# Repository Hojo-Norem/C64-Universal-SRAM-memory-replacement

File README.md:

# C64-Universal-SRAM-memory-replacement
Replace that old unreliable DRAM in your C64 with SRAM!

Inspired by penfold42 on the Lemon64 forum.

Bonus for shortboard users!
---------------------------------------
Testing so far has shown that this mod eliminates the VSP bug!

The main goal of this little experiment is to see if the SRAM has any immunity to the VIC-II VSP bug that plagues many shortboard C64s and some longboard C64s.

This board has been designed to fit under the character generator ROM on either the long or short motherboards.  It will also work in the KERNAL and BASIC sockets on the long board.

Basic construction
-------------------------

64KB, 128KB and 256KB SRAMs in a "SOP32L" or similar package,  are compatible as long as they conform to the standard pinout.  64KB SRAMS can be harvested (carefully) from SNES Stuntrace FX and DooM carts.  128KB SRAMS are still relatively easy to come by new (as of 2016).  Use those, cause destroying working carts for parts is a crime...  Okay, it /should/ be. 

C1 and C2 are basic power bypass caps.  I just used some spare 100nf parts I had lying around.

The small IC just above the caps is a single inverter gate.  There are differing part numbers among the various manufactures, but what you are looking for is a inverter in a SOT23-5 package designed for 5V operation.  It would probably help to get the TTL compatible version.  The part number printed (74HCT1G04) is a guide only.

Header Wiring
--------------------
Pins 1,3,4 & 5 connect the the motherboard's DRAM address lines MA4, MA5, MA6 & MA7.  For the 4146s used on most longboards, these are pins 9,10,11 & 13.  For the 41464 used on the shortboards and later longboards, use pins 7,8,10 & 14.  Do not cross check these with the datasheets as Commodore did not.  Following the datasheet (for the 41464 at least) will result in screen corruption and a lower bytes free reported on bootup.  These can be connected in any order, Commodore didn't care and so doesn't the memory!

Pin 2 is connected to the DRAM R/W line, which is pin 3 and 4 for the 4146 and 41464 respectively.

Pin 6 is connected to the DRAM CAS line.  Pin 15 for the 4146 and pin 16 for the 41464.

Finally, pin 7 is connected to the DRAM RAS line.  Pin 4 for the 4146 and pin 5 for the 41464.

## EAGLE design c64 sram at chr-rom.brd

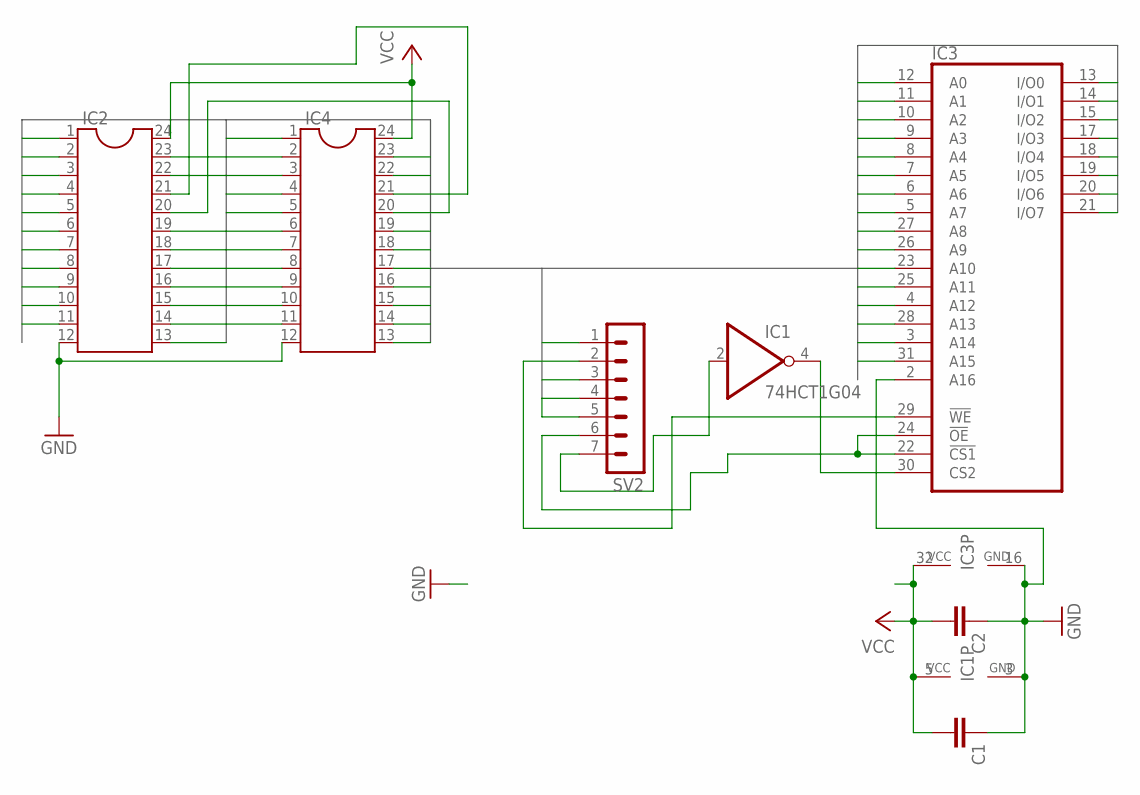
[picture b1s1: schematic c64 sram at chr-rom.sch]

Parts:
C1, C2: C-EUC0805; C0805
IC1: 74HCT1G04; SOT23-5
IC2, IC4: DIL24-6
IC3: LP621024CM; SOP32L
SV2: MA07-1

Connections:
A0: IC2.8, IC3.12 (A0), IC4.8
A1: IC2.7, IC3.11 (A1), IC4.7
A2: IC2.6, IC3.10 (A2), IC4.6
A3: IC2.5, IC3.9 (A3), IC4.5
A4: IC2.4, IC3.8 (A4), IC4.4
A5: IC2.3, IC3.7 (A5), IC4.3
A6: IC2.2, IC3.6 (A6), IC4.2
A7: IC2.1, IC3.5 (A7), IC4.1
A8: IC2.23, IC3.27 (A8), IC4.23
A9: IC2.22, IC3.26 (A9), IC4.22
A10: IC2.19, IC3.23 (A10), IC4.19
A11: IC2.18, IC3.25 (A11), IC4.18
A12: IC3.4 (A12), SV2.5
A13: IC3.28 (A13), SV2.3
A14: IC3.3 (A14), SV2.4
A15: IC3.31 (A15), SV2.1
D0: IC2.9, IC3.13 (I/O0), IC4.9
D1: IC2.10, IC3.14 (I/O1), IC4.10
D2: IC2.11, IC3.15 (I/O2), IC4.11
D3: IC2.13, IC3.21 (I/O7), IC4.13
D4: IC2.14, IC3.20 (I/O6), IC4.14
D5: IC2.15, IC3.19 (I/O5), IC4.15
D6: IC2.16, IC3.18 (I/O4), IC4.16
D7: IC2.17, IC3.17 (I/O3), IC4.17
GND: C1.1, C2.1, IC1.3 (GND), IC2.12, IC3.2 (A16), IC3.16 (GND), IC4.12
unnamed: IC2.21, IC4.21
unnamed: IC1.4 (O), IC3.30 (CS2)
unnamed: IC2.20, IC4.20
unnamed: IC1.2 (I), SV2.7
unnamed: IC3.22 (!CS1), IC3.24 (!OE), SV2.6
R/_W: IC3.29 (!WE), SV2.2
VCC: C1.2, C2.2, IC1.5 (VCC), IC2.24, IC3.32 (VCC), IC4.24

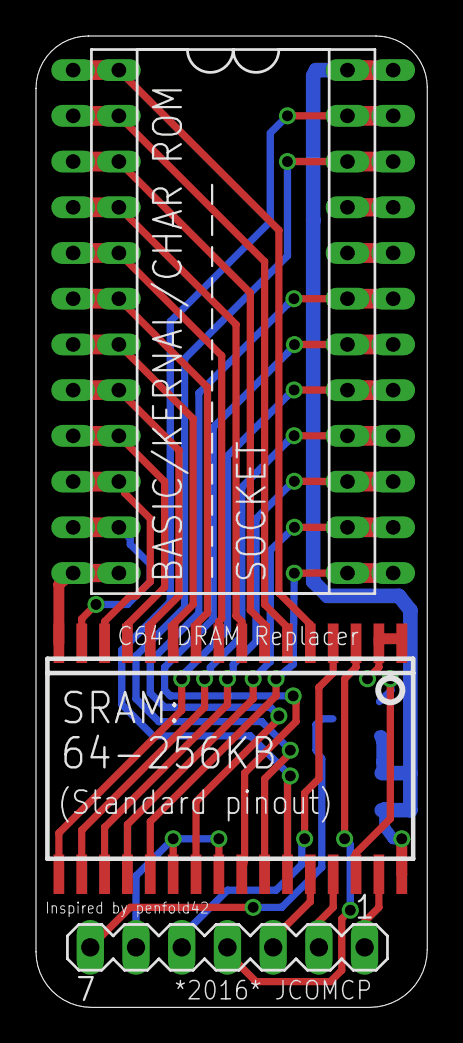
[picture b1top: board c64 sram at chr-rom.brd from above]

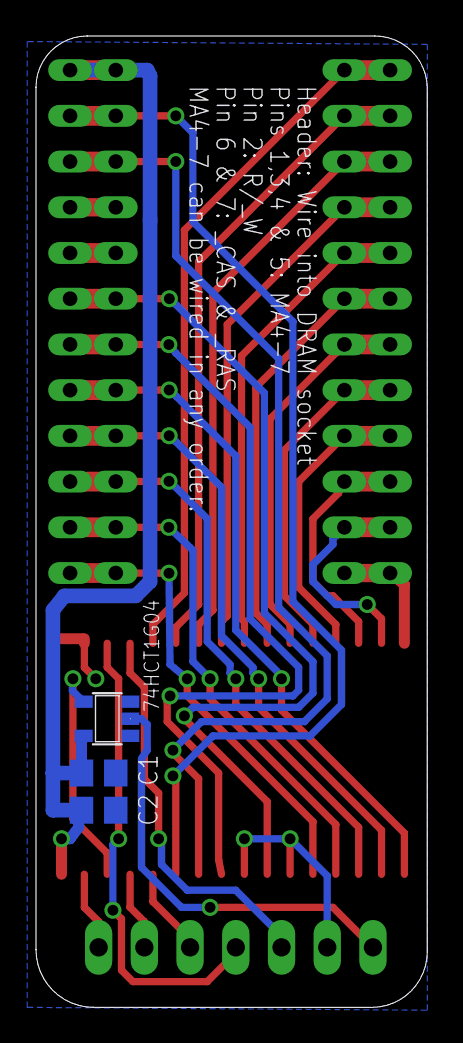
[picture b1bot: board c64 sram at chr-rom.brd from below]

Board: 2 copper layers, 21.7 x 54.0 mm, 7 parts (3 on the bottom side), 32 nets.

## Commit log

2026-05-21 Update README.md
    Copied from OSHPark project description.
2026-05-21 Added Eagle schematic and board files.
    The schematic is untidy T_T
2026-05-21 Update LICENSE
    Altered for suitability for hardware rather than software.
2026-05-21 Photos
2026-05-21 Update README.md
    Added photos
